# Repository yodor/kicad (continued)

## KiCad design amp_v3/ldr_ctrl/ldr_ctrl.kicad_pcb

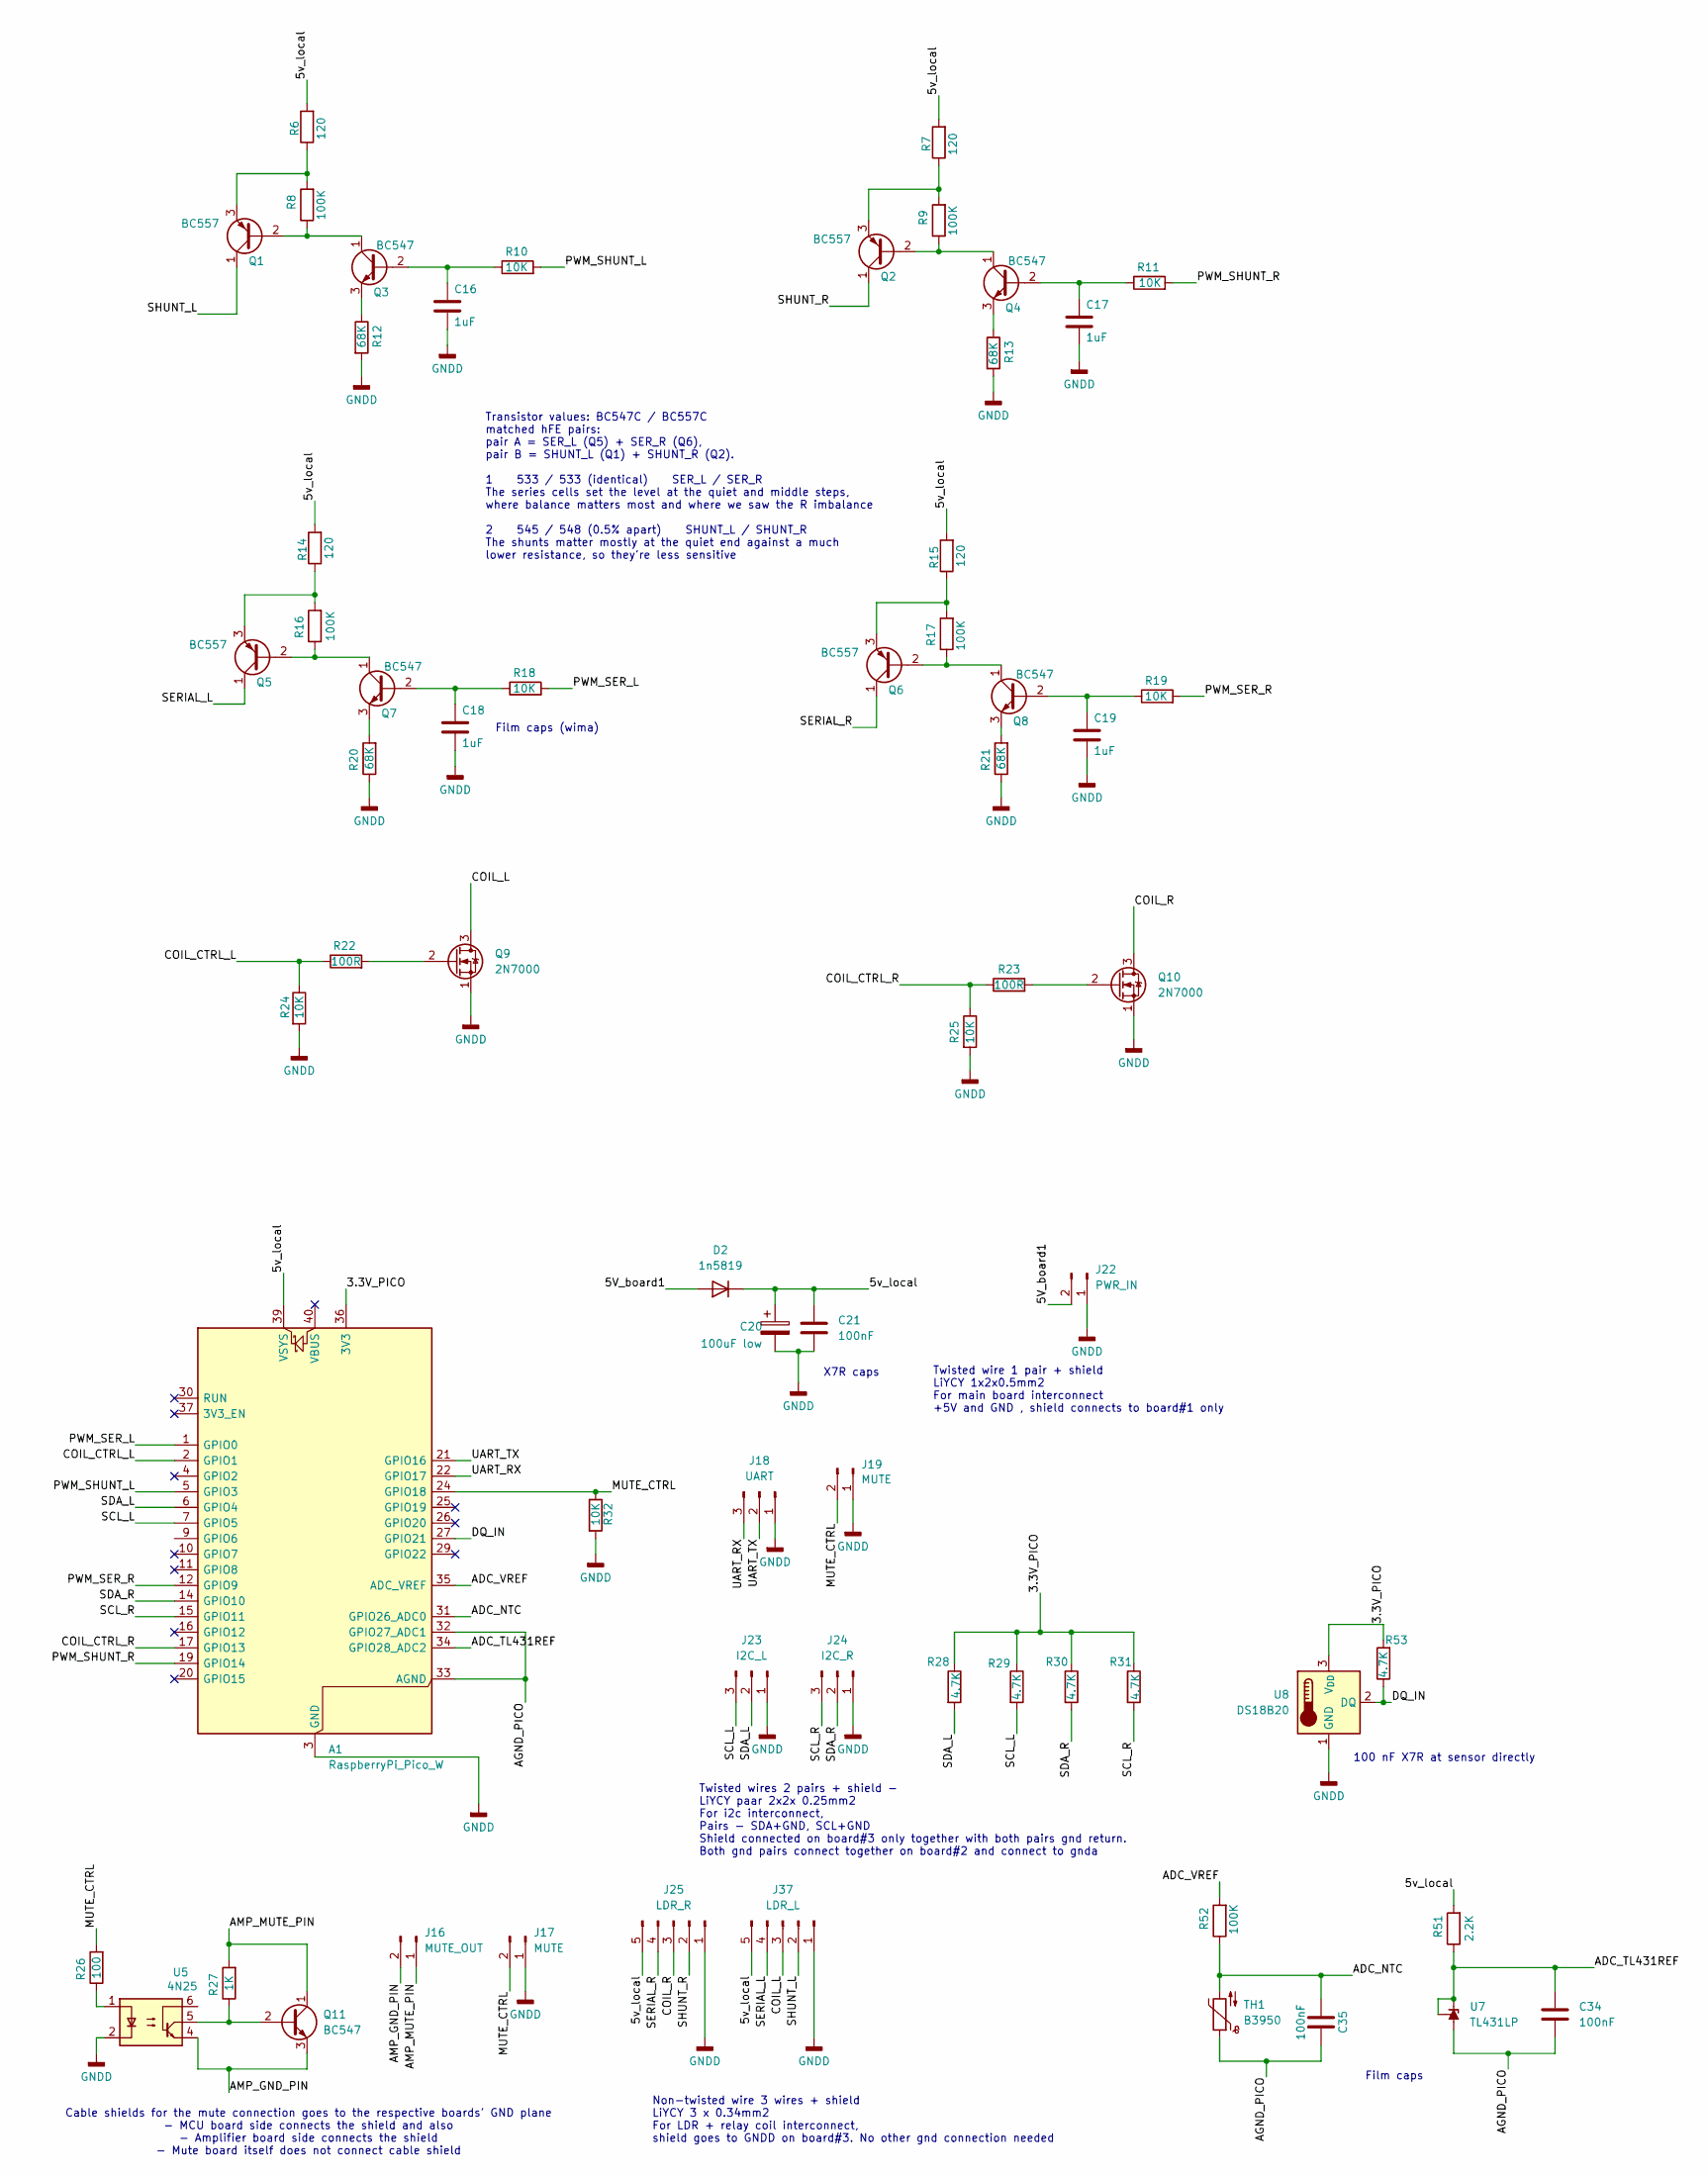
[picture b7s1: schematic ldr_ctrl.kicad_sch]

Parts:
A1: RaspberryPi_Pico_W; RaspberryPi_Pico_Common_THT
C16, C17, C18, C19: 1uF; C_Rect_L7.2mm_W4.5mm_P5.00mm_FKS2_FKP2_MKS2_MKP2
C20: 100uF low; CP_Radial_D6.3mm_P2.50mm
C21: 100nF; C_Disc_D5.0mm_W2.5mm_P5.00mm
C34, C35: 100nF; C_Rect_L7.2mm_W2.5mm_P5.00mm_FKS2_FKP2_MKS2_MKP2
D2: 1n5819; D_DO-41_SOD81_P3.81mm_Vertical_CathodeUp
J16: MUTE_OUT; JST_XH_B2B-XH-A_1x02_P2.50mm_Vertical
J17, J19: MUTE; JST_XH_B2B-XH-A_1x02_P2.50mm_Vertical
J18: UART; JST_XH_B3B-XH-A_1x03_P2.50mm_Vertical
J22: PWR_IN; JST_XH_B2B-XH-A_1x02_P2.50mm_Vertical
J23: I2C_L; JST_XH_B3B-XH-A_1x03_P2.50mm_Vertical
J24: I2C_R; JST_XH_B3B-XH-A_1x03_P2.50mm_Vertical
J25: LDR_R; JST_XH_B5B-XH-A_1x05_P2.50mm_Vertical
J37: LDR_L; JST_XH_B5B-XH-A_1x05_P2.50mm_Vertical
Q1, Q2, Q5, Q6: BC557; TO-92_Inline_Wide
Q3, Q4, Q7, Q8, Q11: BC547; TO-92_Inline_Wide
Q9, Q10: 2N7000; TO-92_Inline_Wide
R6, R7: 120; R_Axial_DIN0207_L6.3mm_D2.5mm_P7.62mm_Horizontal
R8, R9, R16, R17, R52: 100K; R_Axial_DIN0207_L6.3mm_D2.5mm_P7.62mm_Horizontal
R10, R11, R18, R19, R24, R25, R32: 10K; R_Axial_DIN0207_L6.3mm_D2.5mm_P7.62mm_Horizontal
R12, R13, R20, R21: 68K; R_Axial_DIN0207_L6.3mm_D2.5mm_P7.62mm_Horizontal
R14, R15: 120; R_Axial_DIN0207_L6.3mm_D2.5mm_P2.54mm_Vertical
R22, R23: 100R; R_Axial_DIN0207_L6.3mm_D2.5mm_P7.62mm_Horizontal
R26: 100; R_Axial_DIN0207_L6.3mm_D2.5mm_P7.62mm_Horizontal
R27: 1K; R_Axial_DIN0207_L6.3mm_D2.5mm_P7.62mm_Horizontal
R28, R29, R30, R31: 4.7K; R_Axial_DIN0207_L6.3mm_D2.5mm_P7.62mm_Horizontal
R51: 2.2K; R_Axial_DIN0207_L6.3mm_D2.5mm_P7.62mm_Horizontal
R53: 4.7K; R_Axial_DIN0207_L6.3mm_D2.5mm_P2.54mm_Vertical
TH1: B3950; JST_XH_B2B-XH-A_1x02_P2.50mm_Vertical
U5: 4N25; DIP-6_W7.62mm
U7: TL431LP; TO-92_Inline_Wide
U8: DS18B20; JST_XH_B3B-XH-A_1x03_P2.50mm_Vertical

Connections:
/3.3V_PICO: A1.36 (3V3), R28.1, R29.1, R30.1, R31.1, R53.2, U8.3 (V_{DD})
/5V_board1: D2.2 (A), J22.2
/5v_local: A1.39 (VSYS), C20.1, C21.1, D2.1 (K), J25.5, J37.5, R6.2, R7.2, R14.2, R15.2, R51.2
/ADC_NTC: A1.31 (GPIO26_ADC0), C35.1, R52.1, TH1.2
/ADC_TL431REF: A1.34 (GPIO28_ADC2), C34.1, R51.1, U7.1 (REF), U7.3 (K)
/ADC_VREF: A1.35 (ADC_VREF), R52.2
/AGND_PICO: A1.32 (GPIO27_ADC1), A1.33 (AGND), C34.2, C35.2, TH1.1, U7.2 (A)
/AMP_GND_PIN: J16.2, Q11.3 (E), U5.4
/AMP_MUTE_PIN: J16.1, Q11.1 (C), R27.2
/COIL_CTRL_L: A1.2 (GPIO1), R22.1, R24.1
/COIL_CTRL_R: A1.17 (GPIO13), R23.1, R25.1
/COIL_L: J37.3, Q9.3 (D)
/COIL_R: J25.3, Q10.3 (D)
/DQ_IN: A1.27 (GPIO21), R53.1, U8.2 (DQ)
/MUTE_CTRL: A1.24 (GPIO18), J17.2, J19.2, R26.2, R32.1
/PWM_SER_L: A1.1 (GPIO0), R18.2
/PWM_SER_R: A1.12 (GPIO9), R19.2
/PWM_SHUNT_L: A1.5 (GPIO3), R10.2
/PWM_SHUNT_R: A1.19 (GPIO14), R11.2
/SCL_L: A1.7 (GPIO5), J23.3, R29.2
/SCL_R: A1.15 (GPIO11), J24.3, R31.2
/SDA_L: A1.6 (GPIO4), J23.2, R28.2
/SDA_R: A1.14 (GPIO10), J24.2, R30.2
/SERIAL_L: J37.4, Q5.1 (C)
/SERIAL_R: J25.4, Q6.1 (C)
/SHUNT_L: J37.2, Q1.1 (C)
/SHUNT_R: J25.2, Q2.1 (C)
/UART_RX: A1.22 (GPIO17), J18.3
/UART_TX: A1.21 (GPIO16), J18.2
GNDD: A1.3 (GND), A1.8 (GND), A1.13 (GND), A1.18 (GND), A1.23 (GND), A1.28 (GND), A1.38 (GND), C16.2, C17.2, C18.2, C19.2, C20.2, C21.2, J17.1, J18.1, J19.1, J22.1, J23.1, J24.1, J25.1, J37.1, Q9.1 (S), Q10.1 (S), R12.2, R13.2, R20.1, R21.1, R24.2, R25.2, R32.2, U5.2, U8.1 (GND)
unnamed: Q1.2 (B), Q3.1 (C), R8.1
unnamed: Q1.3 (E), R6.1, R8.2
unnamed: Q2.2 (B), Q4.1 (C), R9.1
unnamed: Q2.3 (E), R7.1, R9.2
unnamed: C16.1, Q3.2 (B), R10.1
unnamed: Q3.3 (E), R12.1
unnamed: C17.1, Q4.2 (B), R11.1
unnamed: Q4.3 (E), R13.1
unnamed: Q5.2 (B), Q7.1 (C), R16.1
unnamed: Q5.3 (E), R14.1, R16.2
unnamed: Q6.2 (B), Q8.1 (C), R17.1
unnamed: Q6.3 (E), R15.1, R17.2
unnamed: C18.1, Q7.2 (B), R18.1
unnamed: Q7.3 (E), R20.2
unnamed: C19.1, Q8.2 (B), R19.1
unnamed: Q8.3 (E), R21.2
unnamed: Q9.2 (G), R22.2
unnamed: Q10.2 (G), R23.2
unnamed: Q11.2 (B), R27.1, U5.5
unnamed: R26.1, U5.1

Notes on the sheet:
100 nF X7R at sensor directly
Twisted wire 1 pair + shield LiYCY 1x2x0.5mm2 For main board interconnect +5V and GND , shield connects to board#1 only
X7R caps
Film caps
Cable shields for the mute connection goes to the respective boards' GND plane - MCU board side connects the shield and also - Amplifier board side connects the shield - Mute board itself does not connect cable shield
Twisted wires 2 pairs + shield - LiYCY paar 2x2x 0.25mm2 For i2c interconnect, Pairs - SDA+GND, SCL+GND Shield connected on board#3 only together with both pairs gnd return. Both gnd pairs connect together on board#2 and connect to gnda
Transistor values: BC547C / BC557C matched hFE pairs: pair A = SER_L (Q5) + SER_R (Q6), pair B = SHUNT_L (Q1) + SHUNT_R (Q2). 1 533 / 533 (identical) SER_L / SER_R The series cells set the level at the quiet and middle steps, where balance matters most and where we saw the R imbalance 2 545 / 548 (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
Film caps (wima)
Non-twisted wire 3 wires + shield LiYCY 3 x 0.34mm2 For LDR + relay coil interconnect, shield goes to GNDD on board#3. No other gnd connection needed

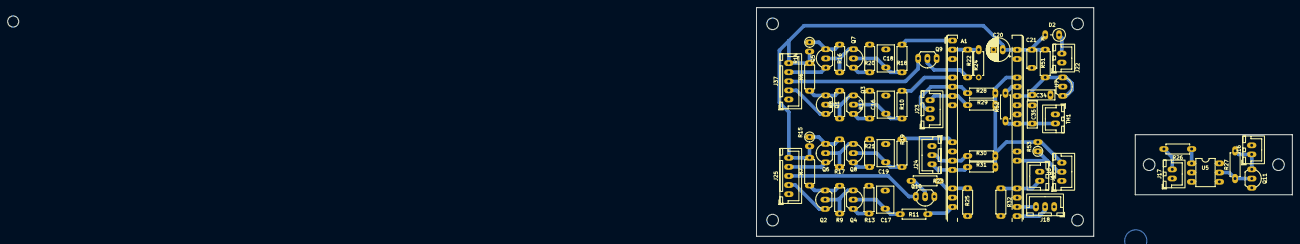
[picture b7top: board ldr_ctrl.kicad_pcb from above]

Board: 2 copper layers, 92.7 x 62.9 mm, 64 parts (0 on the bottom side), 50 nets.

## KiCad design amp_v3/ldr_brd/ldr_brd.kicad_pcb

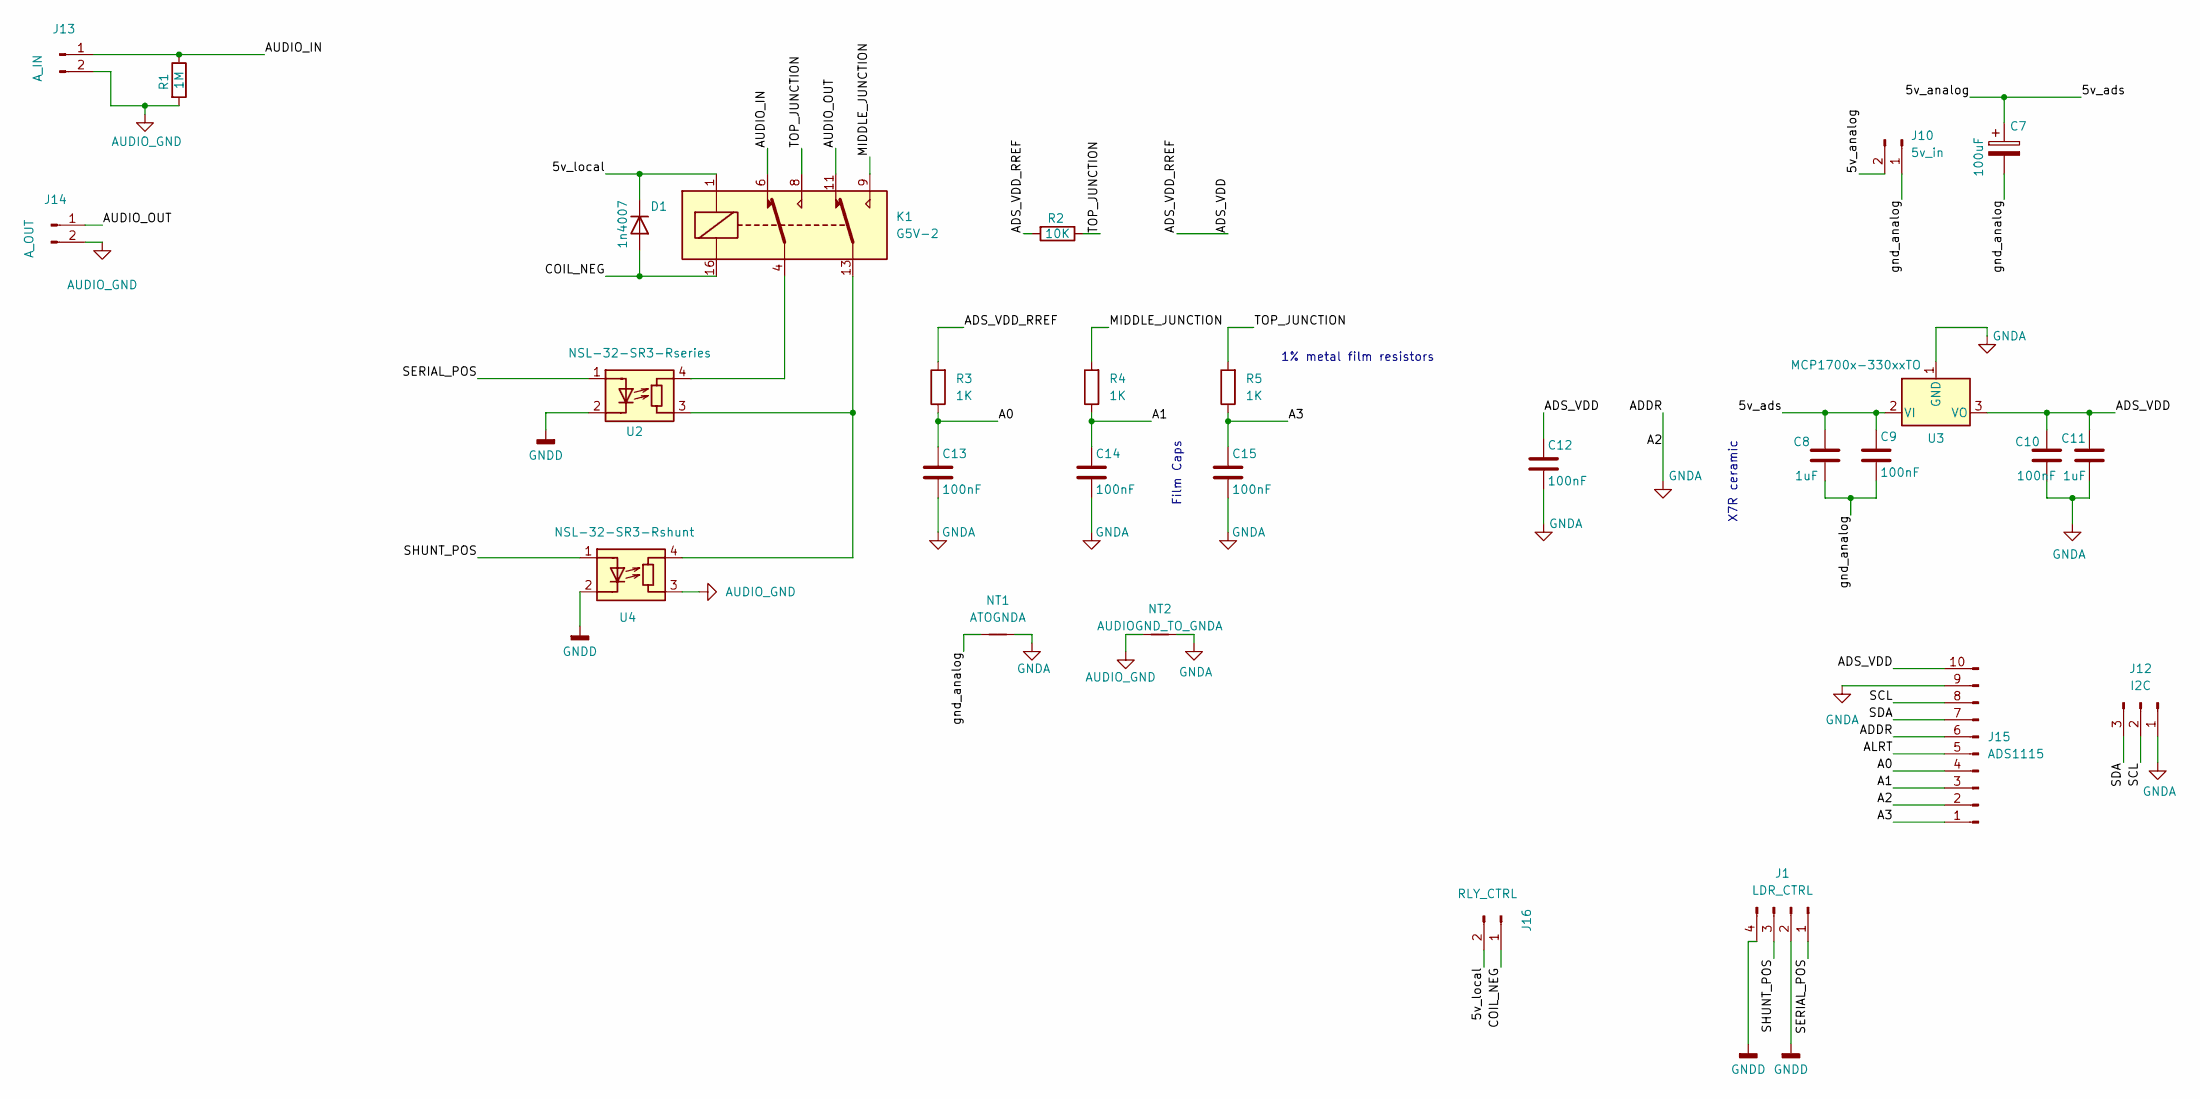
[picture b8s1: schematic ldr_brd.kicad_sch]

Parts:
C7: 100uF; CP_Radial_D5.0mm_P2.50mm
C8, C11: 1uF; C_Disc_D5.0mm_W2.5mm_P5.00mm
C9, C10, C12: 100nF; C_Disc_D5.0mm_W2.5mm_P5.00mm
C13, C14, C15: 100nF; C_Rect_L7.2mm_W2.5mm_P5.00mm_FKS2_FKP2_MKS2_MKP2
D1: 1n4007; D_DO-35_SOD27_P7.62mm_Horizontal
J1: LDR_CTRL; JST_XH_B4B-XH-A_1x04_P2.50mm_Vertical
J10: 5v_in; JST_XH_B2B-XH-A_1x02_P2.50mm_Vertical
J12: I2C; JST_XH_B3B-XH-A_1x03_P2.50mm_Vertical
J13: A_IN; JST_XH_B2B-XH-A_1x02_P2.50mm_Vertical
J14: A_OUT; JST_XH_B2B-XH-A_1x02_P2.50mm_Vertical
J15: ADS1115; PinSocket_1x10_P2.54mm_Vertical
J16: RLY_CTRL; JST_XH_B2B-XH-A_1x02_P2.50mm_Vertical
K1: G5V-2; Relay_DPDT_Omron_G5V-2
NT1: ATOGNDA; NetTie-2_SMD_Pad1.0o
NT2: AUDIOGND_TO_GNDA; NetTie-2_SMD_Pad1.0o
R1: 1M; R_Axial_DIN0207_L6.3mm_D2.5mm_P2.54mm_Vertical
R2: 10K; R_Axial_DIN0207_L6.3mm_D2.5mm_P7.62mm_Horizontal
R3, R4, R5: 1K; R_Axial_DIN0207_L6.3mm_D2.5mm_P7.62mm_Horizontal
U2: NSL-32-SR3-Rseries; Luna_NSL-32
U3: MCP1700x-330xxTO; TO-92_Inline_Wide
U4: NSL-32-SR3-Rshunt; Luna_NSL-32

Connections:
/5v_ads: C7.1, C8.1, C9.1, J10.2, U3.2 (VI)
/5v_local: D1.1 (K), J16.2, K1.1
/A0: C13.1, J15.4, R3.1
/A1: C14.1, J15.3, R4.1
/A3: C15.1, J15.1, R5.1
/ADS_VDD: C10.1, C11.1, C12.1, J15.10, R2.2, R3.2, U3.3 (VO)
/AUDIO_IN: J13.1, K1.6, R1.1
/AUDIO_OUT: J14.1, K1.11
/COIL_NEG: D1.2 (A), J16.1, K1.16
/MIDDLE_JUNCTION: K1.9, R4.2
/SCL: J12.2, J15.8
/SDA: J12.3, J15.7
/SERIAL_POS: J1.1, U2.1 (A)
/SHUNT_POS: J1.3, U4.1 (A)
/TOP_JUNCTION: K1.8, R2.1, R5.2
/gnd_analog: C7.2, C8.2, C9.2, J10.1, NT1.1
AUDIO_GND: J13.2, J14.2, NT2.1, R1.2, U4.3 (R)
GNDA: C10.2, C11.2, C12.2, C13.2, C14.2, C15.2, J12.1, J15.2, J15.6, J15.9, NT1.2, NT2.2, U3.1 (GND)
GNDD: J1.2, J1.4, U2.2 (K), U4.2 (K)
unnamed: K1.4, U2.4 (R)
unnamed: K1.13, U2.3 (R), U4.4 (R)

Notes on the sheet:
X7R ceramic
1% metal film resistors
Film Caps

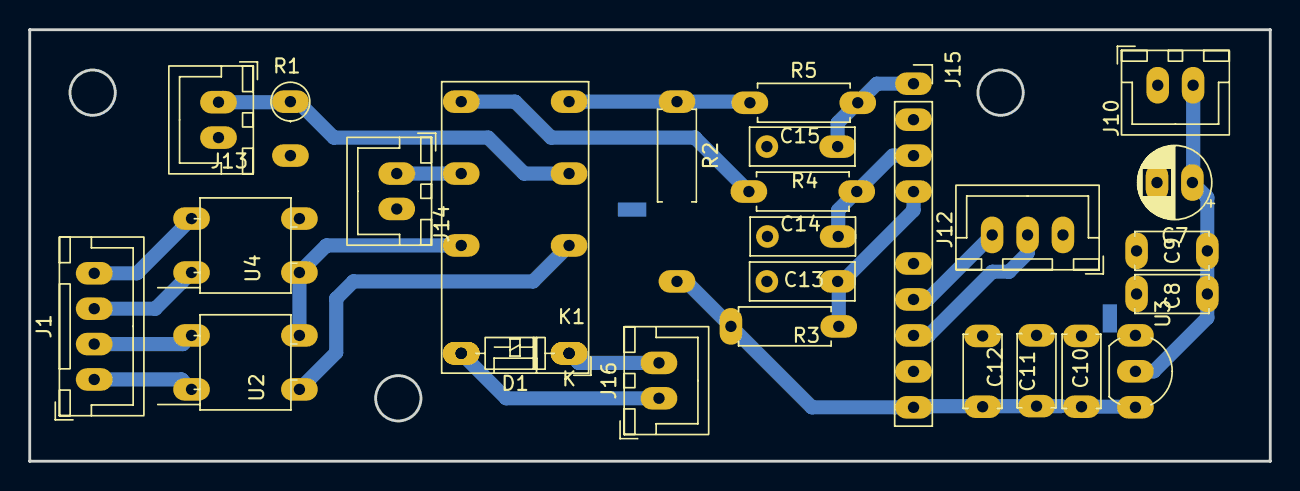
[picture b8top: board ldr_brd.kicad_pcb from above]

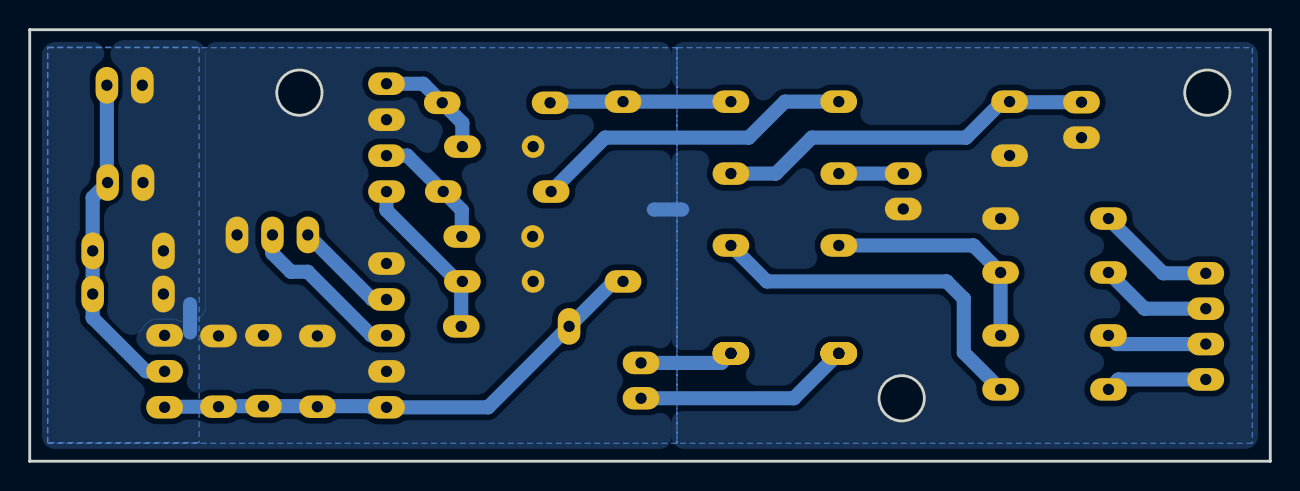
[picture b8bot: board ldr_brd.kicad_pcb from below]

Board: 2 copper layers, 87.6 x 30.5 mm, 28 parts (2 on the bottom side), 21 nets.

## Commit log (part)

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2016-07-28 fixes
2017-01-19 updates,rc_car
2017-02-21 rc-car
2018-12-14 cleanups
2026-06-28 update_v3
